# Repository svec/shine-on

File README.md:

# shine-on
Contextual Electronics Shine On intro PCB design.

Based on: https://contextualelectronics.com/courses/shine-on-you-crazy-kicad/

Oshpark PCB available at: https://oshpark.com/shared_projects/eNvG9DSg

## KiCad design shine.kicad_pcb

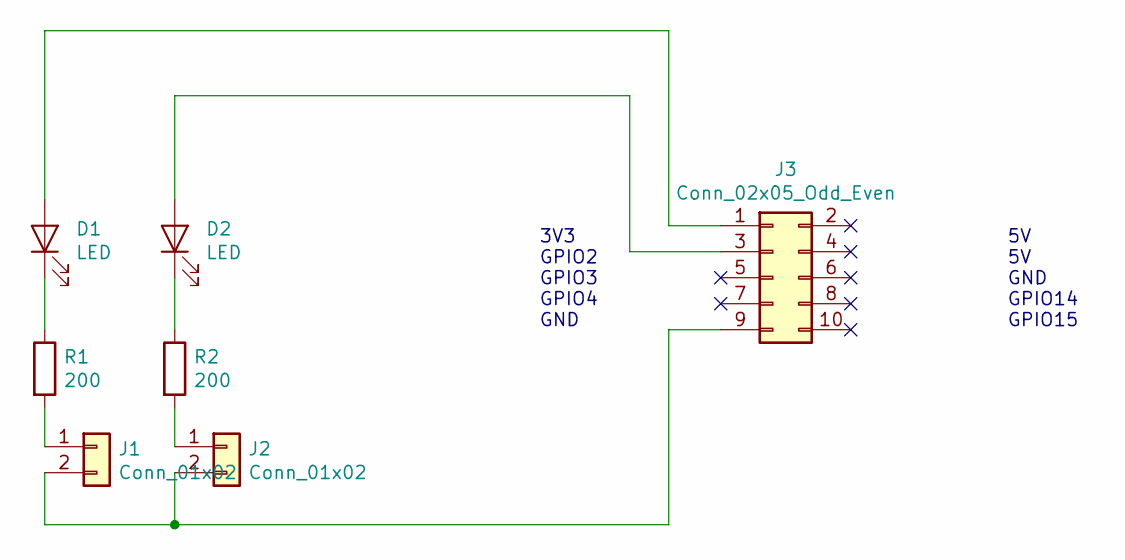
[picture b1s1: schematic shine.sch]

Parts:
D1, D2: LED; LED_1206_3216Metric
J1, J2: Conn_01x02; PinHeader_1x02_P2.54mm_Vertical
J3: Conn_02x05_Odd_Even; PinHeader_2x05_P2.54mm_Vertical
R1, R2: 200; R_1206_3216Metric_Pad1.42x1.75mm_HandSolder

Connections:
unnamed: D1.1 (K), R1.1
unnamed: D1.2 (A), J3.1
unnamed: D2.1 (K), R2.1
unnamed: D2.2 (A), J3.3
unnamed: J1.1, R1.2
unnamed: J1.2, J2.2, J3.9
unnamed: J2.1, R2.2

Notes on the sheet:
3V3 GPIO2 GPIO3 GPIO4 GND
5V 5V GND GPIO14 GPIO15

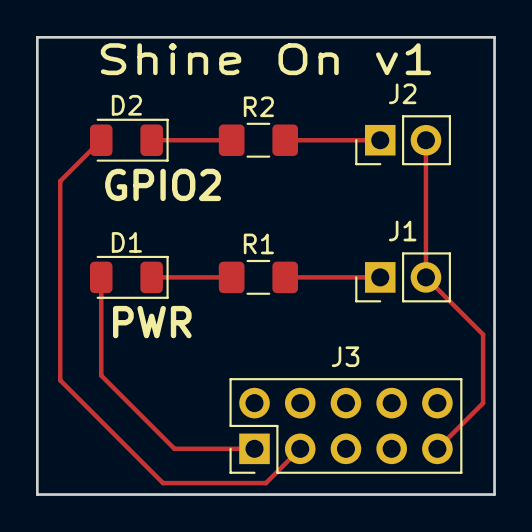
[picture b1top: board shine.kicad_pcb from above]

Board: 2 copper layers, 25.4 x 25.4 mm, 7 parts (0 on the bottom side), 7 nets.

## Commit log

2018-11-17 Added initial project which was sent for fab.
